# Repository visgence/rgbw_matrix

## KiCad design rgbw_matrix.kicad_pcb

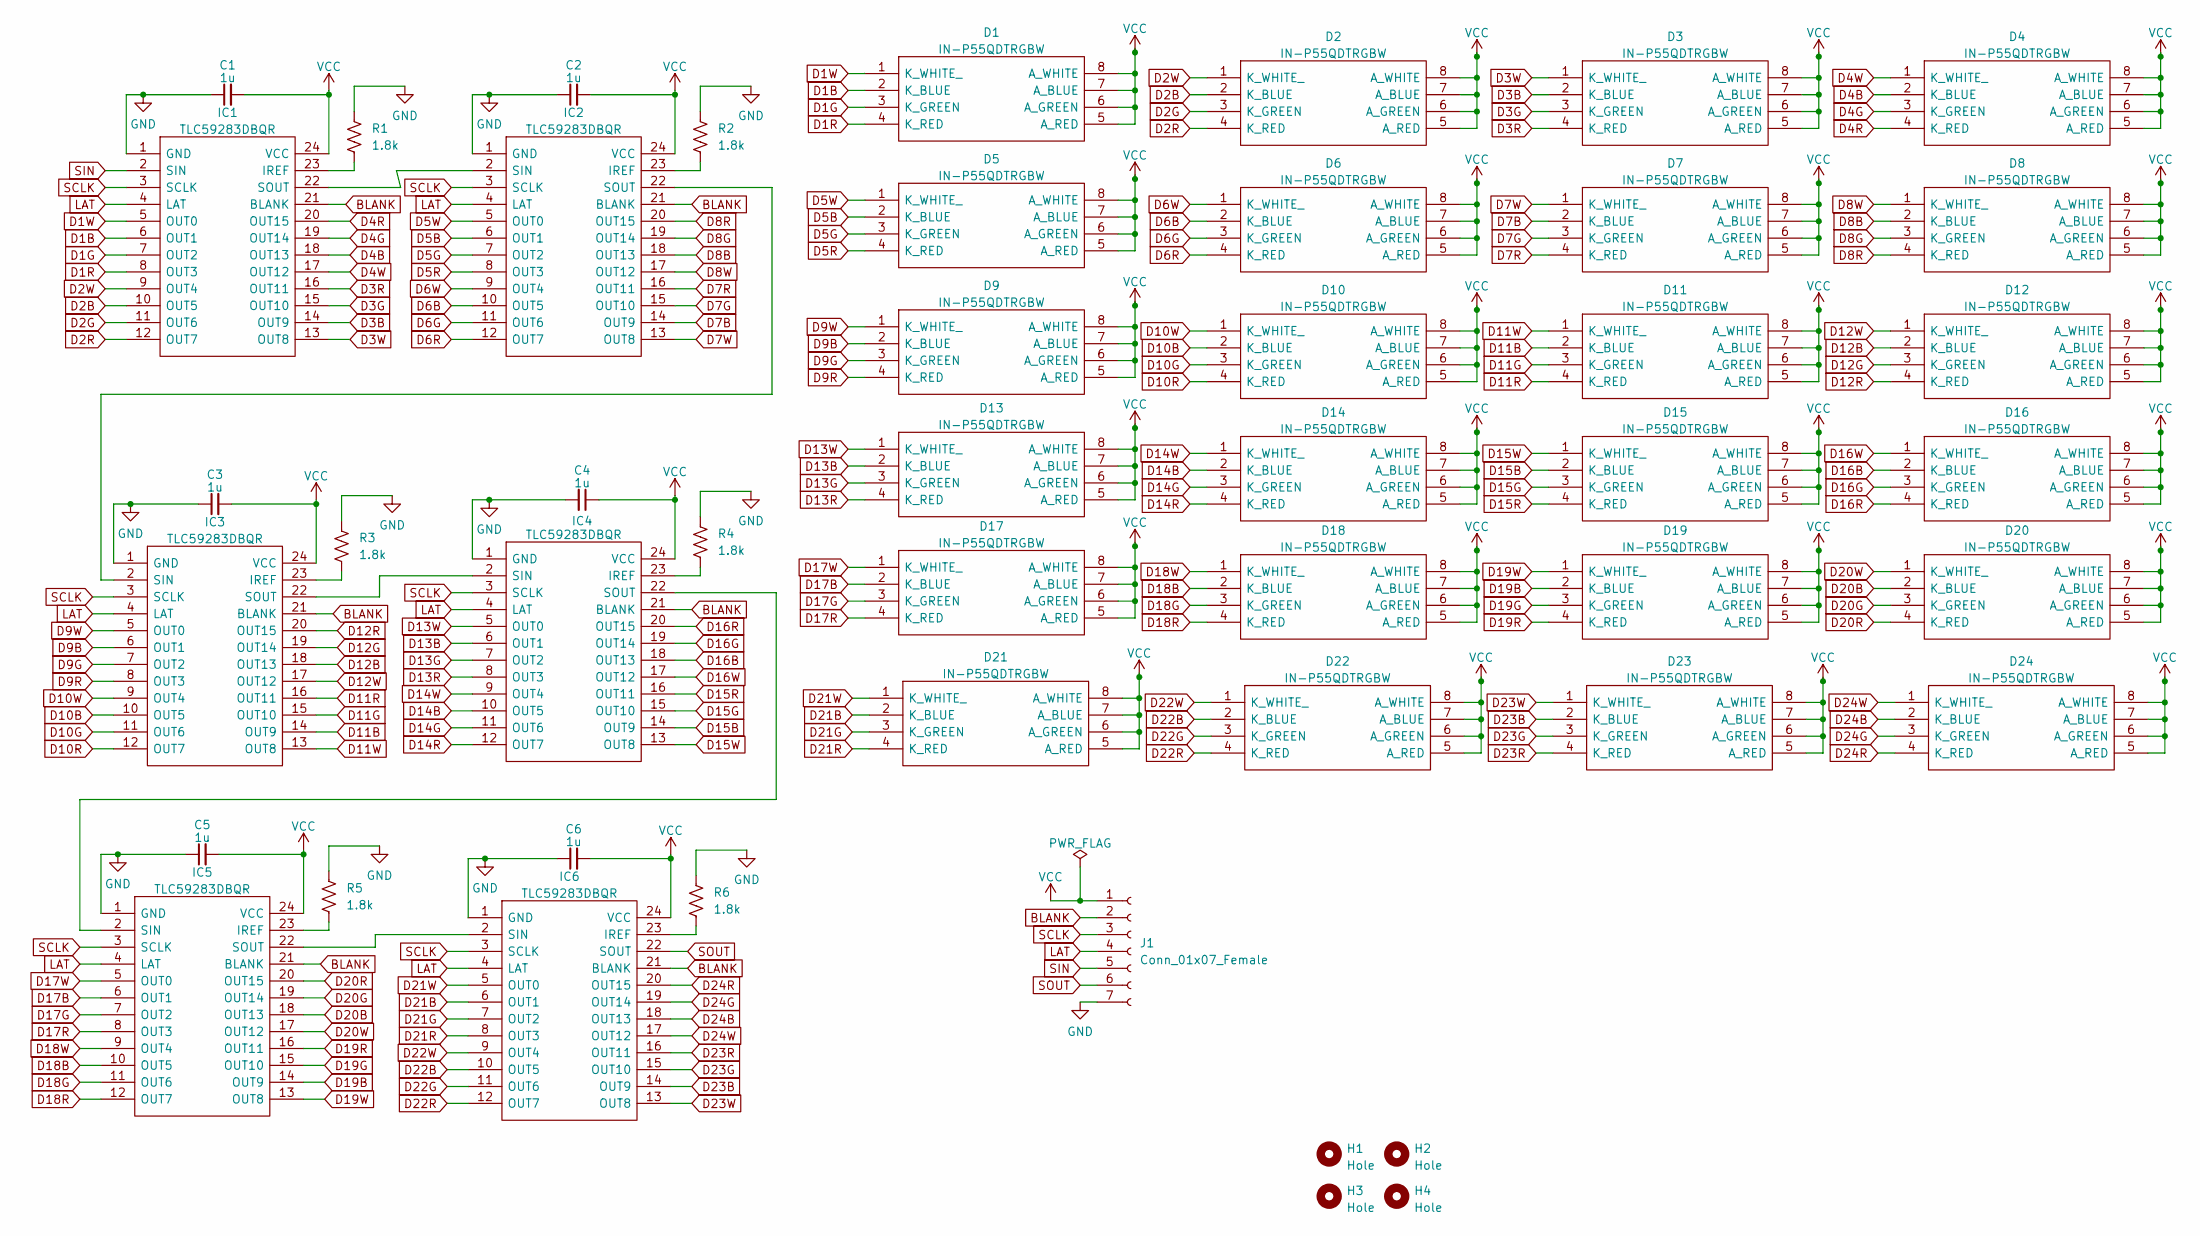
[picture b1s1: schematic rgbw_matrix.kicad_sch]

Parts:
C1, C2, C3, C4, C5, C6: 1u; C_0201_0603Metric
D1, D2, D3, D4, D5, D6, D7, D8, D9, D10, D11, D12, D13, D14, D15, D16, D17, D18, D19, D20, D21, D22, D23, D24: IN-P55QDTRGBW; INP55QDTRGBW; Mouser Part Number 743-IN-P55QDTRGBW
H1, H2, H3, H4: Hole; MountingHole_M3_plated
IC1, IC2, IC3, IC4, IC5, IC6: TLC59283DBQR; SOP64P600X175-24N; Mouser Part Number 595-TLC59283DBQR
J1: Conn_01x07_Female; PinHeader_1x07_P2.54mm_Vertical
R1, R2, R3, R4, R5, R6: 1.8k; R_0201_0603Metric

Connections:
BLANK: IC1.21 (BLANK), IC2.21 (BLANK), IC3.21 (BLANK), IC4.21 (BLANK), IC5.21 (BLANK), IC6.21 (BLANK), J1.2
D1B: D1.2 (K_BLUE), IC1.6 (OUT1)
D1G: D1.3 (K_GREEN), IC1.7 (OUT2)
D1R: D1.4 (K_RED), IC1.8 (OUT3)
D1W: D1.1 (K_WHITE_), IC1.5 (OUT0)
D2B: D2.2 (K_BLUE), IC1.10 (OUT5)
D2G: D2.3 (K_GREEN), IC1.11 (OUT6)
D2R: D2.4 (K_RED), IC1.12 (OUT7)
D2W: D2.1 (K_WHITE_), IC1.9 (OUT4)
D3B: D3.2 (K_BLUE), IC1.14 (OUT9)
D3G: D3.3 (K_GREEN), IC1.15 (OUT10)
D3R: D3.4 (K_RED), IC1.16 (OUT11)
D3W: D3.1 (K_WHITE_), IC1.13 (OUT8)
D4B: D4.2 (K_BLUE), IC1.18 (OUT13)
D4G: D4.3 (K_GREEN), IC1.19 (OUT14)
D4R: D4.4 (K_RED), IC1.20 (OUT15)
D4W: D4.1 (K_WHITE_), IC1.17 (OUT12)
D5B: D5.2 (K_BLUE), IC2.6 (OUT1)
D5G: D5.3 (K_GREEN), IC2.7 (OUT2)
D5R: D5.4 (K_RED), IC2.8 (OUT3)
D5W: D5.1 (K_WHITE_), IC2.5 (OUT0)
D6B: D6.2 (K_BLUE), IC2.10 (OUT5)
D6G: D6.3 (K_GREEN), IC2.11 (OUT6)
D6R: D6.4 (K_RED), IC2.12 (OUT7)
D6W: D6.1 (K_WHITE_), IC2.9 (OUT4)
D7B: D7.2 (K_BLUE), IC2.14 (OUT9)
D7G: D7.3 (K_GREEN), IC2.15 (OUT10)
D7R: D7.4 (K_RED), IC2.16 (OUT11)
D7W: D7.1 (K_WHITE_), IC2.13 (OUT8)
D8B: D8.2 (K_BLUE), IC2.18 (OUT13)
D8G: D8.3 (K_GREEN), IC2.19 (OUT14)
D8R: D8.4 (K_RED), IC2.20 (OUT15)
D8W: D8.1 (K_WHITE_), IC2.17 (OUT12)
D9B: D9.2 (K_BLUE), IC3.6 (OUT1)
D9G: D9.3 (K_GREEN), IC3.7 (OUT2)
D9R: D9.4 (K_RED), IC3.8 (OUT3)
D9W: D9.1 (K_WHITE_), IC3.5 (OUT0)
D10B: D10.2 (K_BLUE), IC3.10 (OUT5)
D10G: D10.3 (K_GREEN), IC3.11 (OUT6)
D10R: D10.4 (K_RED), IC3.12 (OUT7)
D10W: D10.1 (K_WHITE_), IC3.9 (OUT4)
D11B: D11.2 (K_BLUE), IC3.14 (OUT9)
D11G: D11.3 (K_GREEN), IC3.15 (OUT10)
D11R: D11.4 (K_RED), IC3.16 (OUT11)
D11W: D11.1 (K_WHITE_), IC3.13 (OUT8)
D12B: D12.2 (K_BLUE), IC3.18 (OUT13)
D12G: D12.3 (K_GREEN), IC3.19 (OUT14)
D12R: D12.4 (K_RED), IC3.20 (OUT15)
D12W: D12.1 (K_WHITE_), IC3.17 (OUT12)
D13B: D13.2 (K_BLUE), IC4.6 (OUT1)
D13G: D13.3 (K_GREEN), IC4.7 (OUT2)
D13R: D13.4 (K_RED), IC4.8 (OUT3)
D13W: D13.1 (K_WHITE_), IC4.5 (OUT0)
D14B: D14.2 (K_BLUE), IC4.10 (OUT5)
D14G: D14.3 (K_GREEN), IC4.11 (OUT6)
D14R: D14.4 (K_RED), IC4.12 (OUT7)
D14W: D14.1 (K_WHITE_), IC4.9 (OUT4)
D15B: D15.2 (K_BLUE), IC4.14 (OUT9)
D15G: D15.3 (K_GREEN), IC4.15 (OUT10)
D15R: D15.4 (K_RED), IC4.16 (OUT11)
D15W: D15.1 (K_WHITE_), IC4.13 (OUT8)
D16B: D16.2 (K_BLUE), IC4.18 (OUT13)
D16G: D16.3 (K_GREEN), IC4.19 (OUT14)
D16R: D16.4 (K_RED), IC4.20 (OUT15)
D16W: D16.1 (K_WHITE_), IC4.17 (OUT12)
D17B: D17.2 (K_BLUE), IC5.6 (OUT1)
D17G: D17.3 (K_GREEN), IC5.7 (OUT2)
D17R: D17.4 (K_RED), IC5.8 (OUT3)
D17W: D17.1 (K_WHITE_), IC5.5 (OUT0)
D18B: D18.2 (K_BLUE), IC5.10 (OUT5)
D18G: D18.3 (K_GREEN), IC5.11 (OUT6)
D18R: D18.4 (K_RED), IC5.12 (OUT7)
D18W: D18.1 (K_WHITE_), IC5.9 (OUT4)
D19B: D19.2 (K_BLUE), IC5.14 (OUT9)
D19G: D19.3 (K_GREEN), IC5.15 (OUT10)
D19R: D19.4 (K_RED), IC5.16 (OUT11)
D19W: D19.1 (K_WHITE_), IC5.13 (OUT8)
D20B: D20.2 (K_BLUE), IC5.18 (OUT13)
D20G: D20.3 (K_GREEN), IC5.19 (OUT14)
D20R: D20.4 (K_RED), IC5.20 (OUT15)
D20W: D20.1 (K_WHITE_), IC5.17 (OUT12)
D21B: D21.2 (K_BLUE), IC6.6 (OUT1)
D21G: D21.3 (K_GREEN), IC6.7 (OUT2)
D21R: D21.4 (K_RED), IC6.8 (OUT3)
D21W: D21.1 (K_WHITE_), IC6.5 (OUT0)
D22B: D22.2 (K_BLUE), IC6.10 (OUT5)
D22G: D22.3 (K_GREEN), IC6.11 (OUT6)
D22R: D22.4 (K_RED), IC6.12 (OUT7)
D22W: D22.1 (K_WHITE_), IC6.9 (OUT4)
D23B: D23.2 (K_BLUE), IC6.14 (OUT9)
D23G: D23.3 (K_GREEN), IC6.15 (OUT10)
D23R: D23.4 (K_RED), IC6.16 (OUT11)
D23W: D23.1 (K_WHITE_), IC6.13 (OUT8)
D24B: D24.2 (K_BLUE), IC6.18 (OUT13)
D24G: D24.3 (K_GREEN), IC6.19 (OUT14)
D24R: D24.4 (K_RED), IC6.20 (OUT15)
D24W: D24.1 (K_WHITE_), IC6.17 (OUT12)
GND: C1.1, C2.1, C3.1, C4.2, C5.1, C6.1, IC1.1 (GND), IC2.1 (GND), IC3.1 (GND), IC4.1 (GND), IC5.1 (GND), IC6.1 (GND), J1.7, R1.1, R2.1, R3.1, R4.1, R5.1, R6.1
LAT: IC1.4 (LAT), IC2.4 (LAT), IC3.4 (LAT), IC4.4 (LAT), IC5.4 (LAT), IC6.4 (LAT), J1.4
unnamed: IC1.22 (SOUT), IC2.2 (SIN)
unnamed: IC1.23 (IREF), R1.2
unnamed: IC2.22 (SOUT), IC3.2 (SIN)
unnamed: IC2.23 (IREF), R2.2
unnamed: IC3.22 (SOUT), IC4.2 (SIN)
unnamed: IC3.23 (IREF), R3.2
unnamed: IC4.22 (SOUT), IC5.2 (SIN)
unnamed: IC4.23 (IREF), R4.2
unnamed: IC5.22 (SOUT), IC6.2 (SIN)
unnamed: IC5.23 (IREF), R5.2
unnamed: IC6.23 (IREF), R6.2
SCLK: IC1.3 (SCLK), IC2.3 (SCLK), IC3.3 (SCLK), IC4.3 (SCLK), IC5.3 (SCLK), IC6.3 (SCLK), J1.3
SIN: IC1.2 (SIN), J1.5
SOUT: IC6.22 (SOUT), J1.6
VCC: C1.2, C2.2, C3.2, C4.1, C5.2, C6.2, D1.5 (A_RED), D1.6 (A_GREEN), D1.7 (A_BLUE), D1.8 (A_WHITE), D2.5 (A_RED), D2.6 (A_GREEN), D2.7 (A_BLUE), D2.8 (A_WHITE), D3.5 (A_RED), D3.6 (A_GREEN), D3.7 (A_BLUE), D3.8 (A_WHITE), D4.5 (A_RED), D4.6 (A_GREEN), D4.7 (A_BLUE), D4.8 (A_WHITE), D5.5 (A_RED), D5.6 (A_GREEN), D5.7 (A_BLUE), D5.8 (A_WHITE), D6.5 (A_RED), D6.6 (A_GREEN), D6.7 (A_BLUE), D6.8 (A_WHITE), D7.5 (A_RED), D7.6 (A_GREEN), D7.7 (A_BLUE), D7.8 (A_WHITE), D8.5 (A_RED), D8.6 (A_GREEN), D8.7 (A_BLUE), D8.8 (A_WHITE), D9.5 (A_RED), D9.6 (A_GREEN), D9.7 (A_BLUE), D9.8 (A_WHITE), D10.5 (A_RED), D10.6 (A_GREEN), D10.7 (A_BLUE), D10.8 (A_WHITE), D11.5 (A_RED), D11.6 (A_GREEN), D11.7 (A_BLUE), D11.8 (A_WHITE), D12.5 (A_RED), D12.6 (A_GREEN), D12.7 (A_BLUE), D12.8 (A_WHITE), D13.5 (A_RED), D13.6 (A_GREEN), D13.7 (A_BLUE), D13.8 (A_WHITE), D14.5 (A_RED), D14.6 (A_GREEN), D14.7 (A_BLUE), D14.8 (A_WHITE), D15.5 (A_RED), D15.6 (A_GREEN), D15.7 (A_BLUE), D15.8 (A_WHITE), D16.5 (A_RED), D16.6 (A_GREEN), D16.7 (A_BLUE), D16.8 (A_WHITE), D17.5 (A_RED), D17.6 (A_GREEN), D17.7 (A_BLUE), D17.8 (A_WHITE), D18.5 (A_RED), D18.6 (A_GREEN), D18.7 (A_BLUE), D18.8 (A_WHITE), D19.5 (A_RED), D19.6 (A_GREEN), D19.7 (A_BLUE), D19.8 (A_WHITE), D20.5 (A_RED), D20.6 (A_GREEN), D20.7 (A_BLUE), D20.8 (A_WHITE), D21.5 (A_RED), D21.6 (A_GREEN), D21.7 (A_BLUE), D21.8 (A_WHITE), D22.5 (A_RED), D22.6 (A_GREEN), D22.7 (A_BLUE), D22.8 (A_WHITE), D23.5 (A_RED), D23.6 (A_GREEN), D23.7 (A_BLUE), D23.8 (A_WHITE), D24.5 (A_RED), D24.6 (A_GREEN), D24.7 (A_BLUE), D24.8 (A_WHITE), IC1.24 (VCC), IC2.24 (VCC), IC3.24 (VCC), IC4.24 (VCC), IC5.24 (VCC), IC6.24 (VCC), J1.1

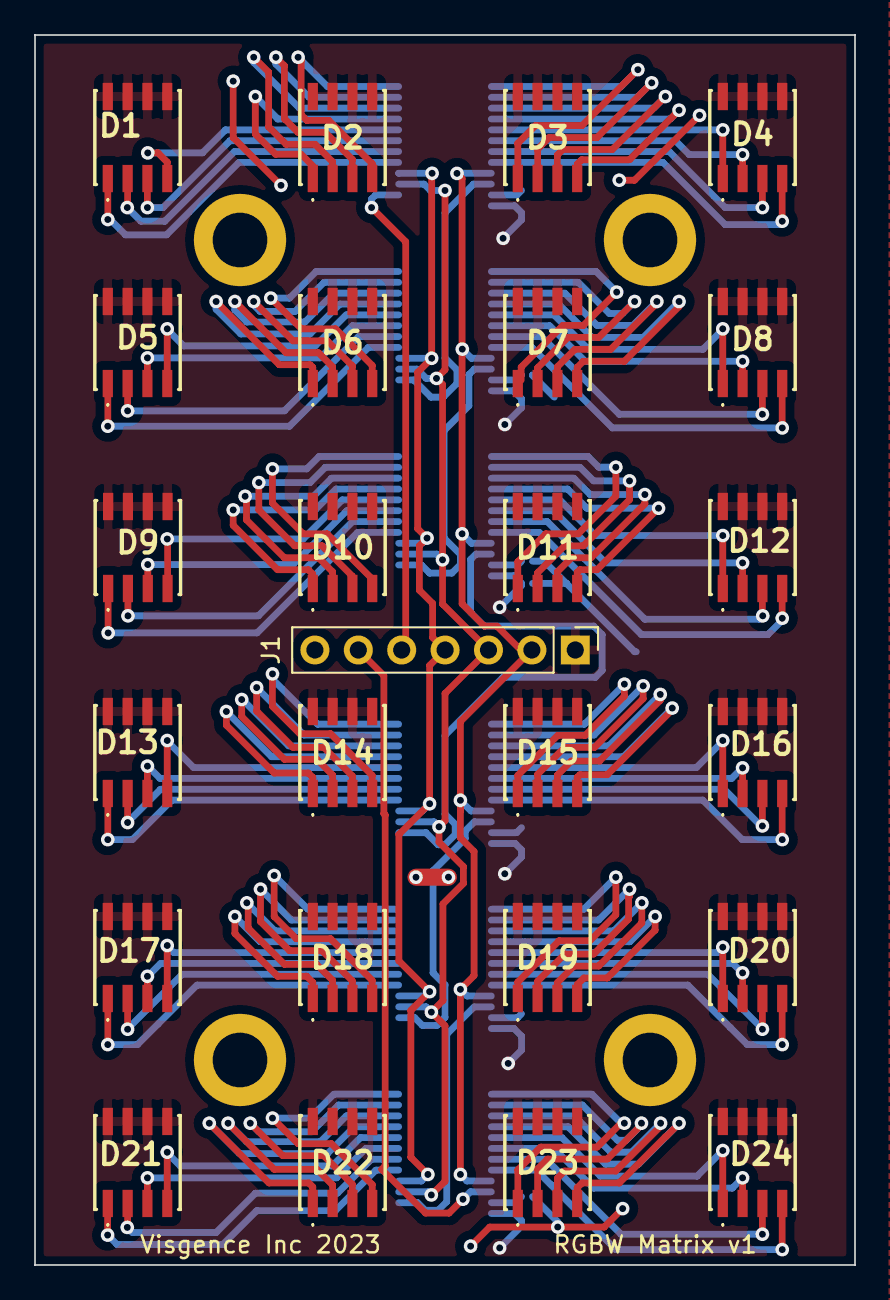
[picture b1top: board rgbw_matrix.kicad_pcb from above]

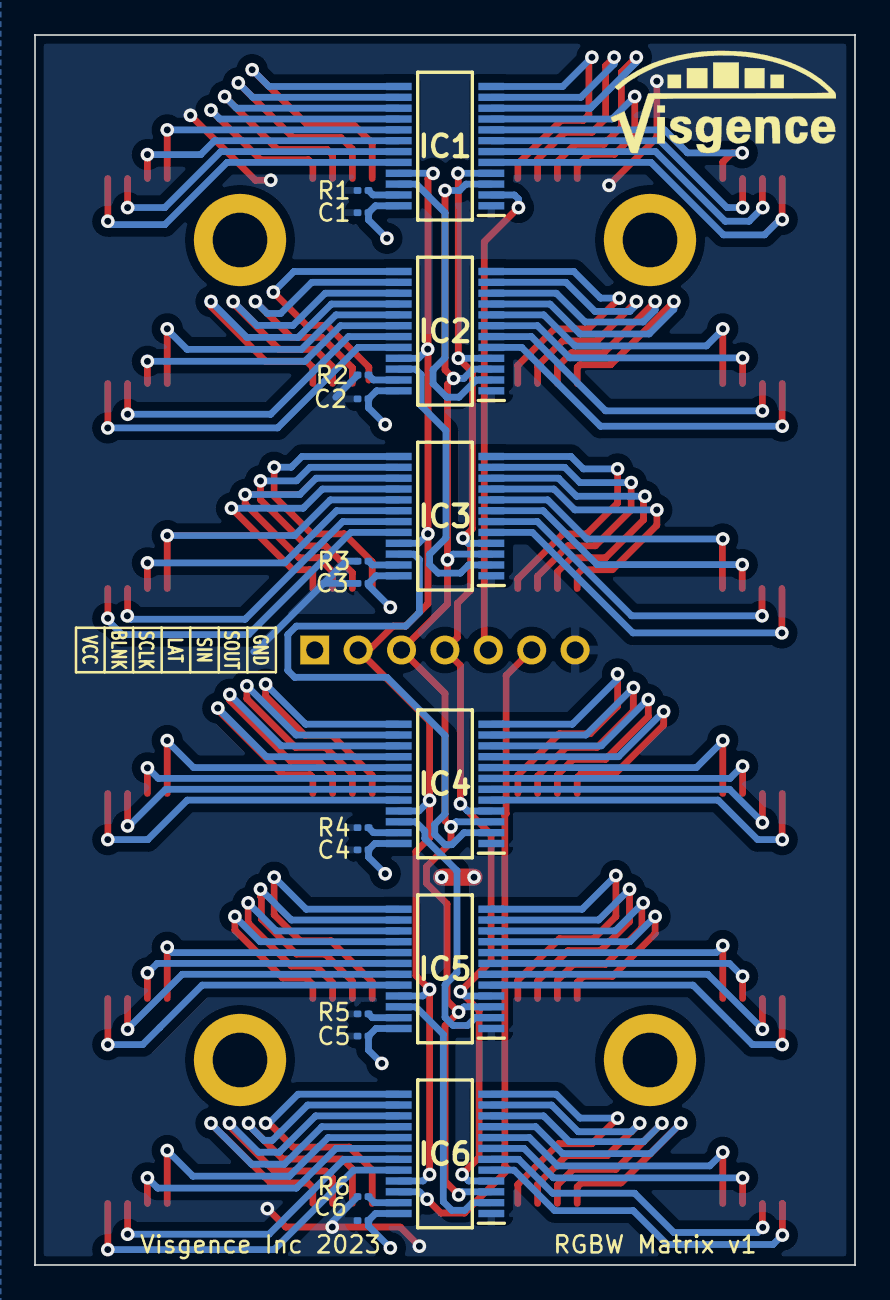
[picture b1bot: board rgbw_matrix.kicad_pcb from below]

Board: 2 copper layers, 48.0 x 72.0 mm, 48 parts (19 on the bottom side), 114 nets.

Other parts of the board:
G: LOGO; LOGO_SMALL

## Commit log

2023-03-02 First commit of new project
2023-03-02 Fix readme
2023-03-02 Added some more componets to schematic
2023-03-02 Did a little more schematic routing
2023-03-06 components connected v1
2023-03-06 components connected v1.1
2023-03-07 Added power flag, corrected capacitor on one chip need to do the others
2023-03-07 capacitors fixed
2023-03-08 Added visgence logo to repo
2023-03-08 added silkscreen text
2023-03-13 track and via improment
2023-03-16 via and track realignment
2023-04-20 Added micropython test code
2023-04-21 adds test script with example screenbuffer and color masks
